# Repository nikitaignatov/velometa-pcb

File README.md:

# velometa pcb

Here be pcb stuff

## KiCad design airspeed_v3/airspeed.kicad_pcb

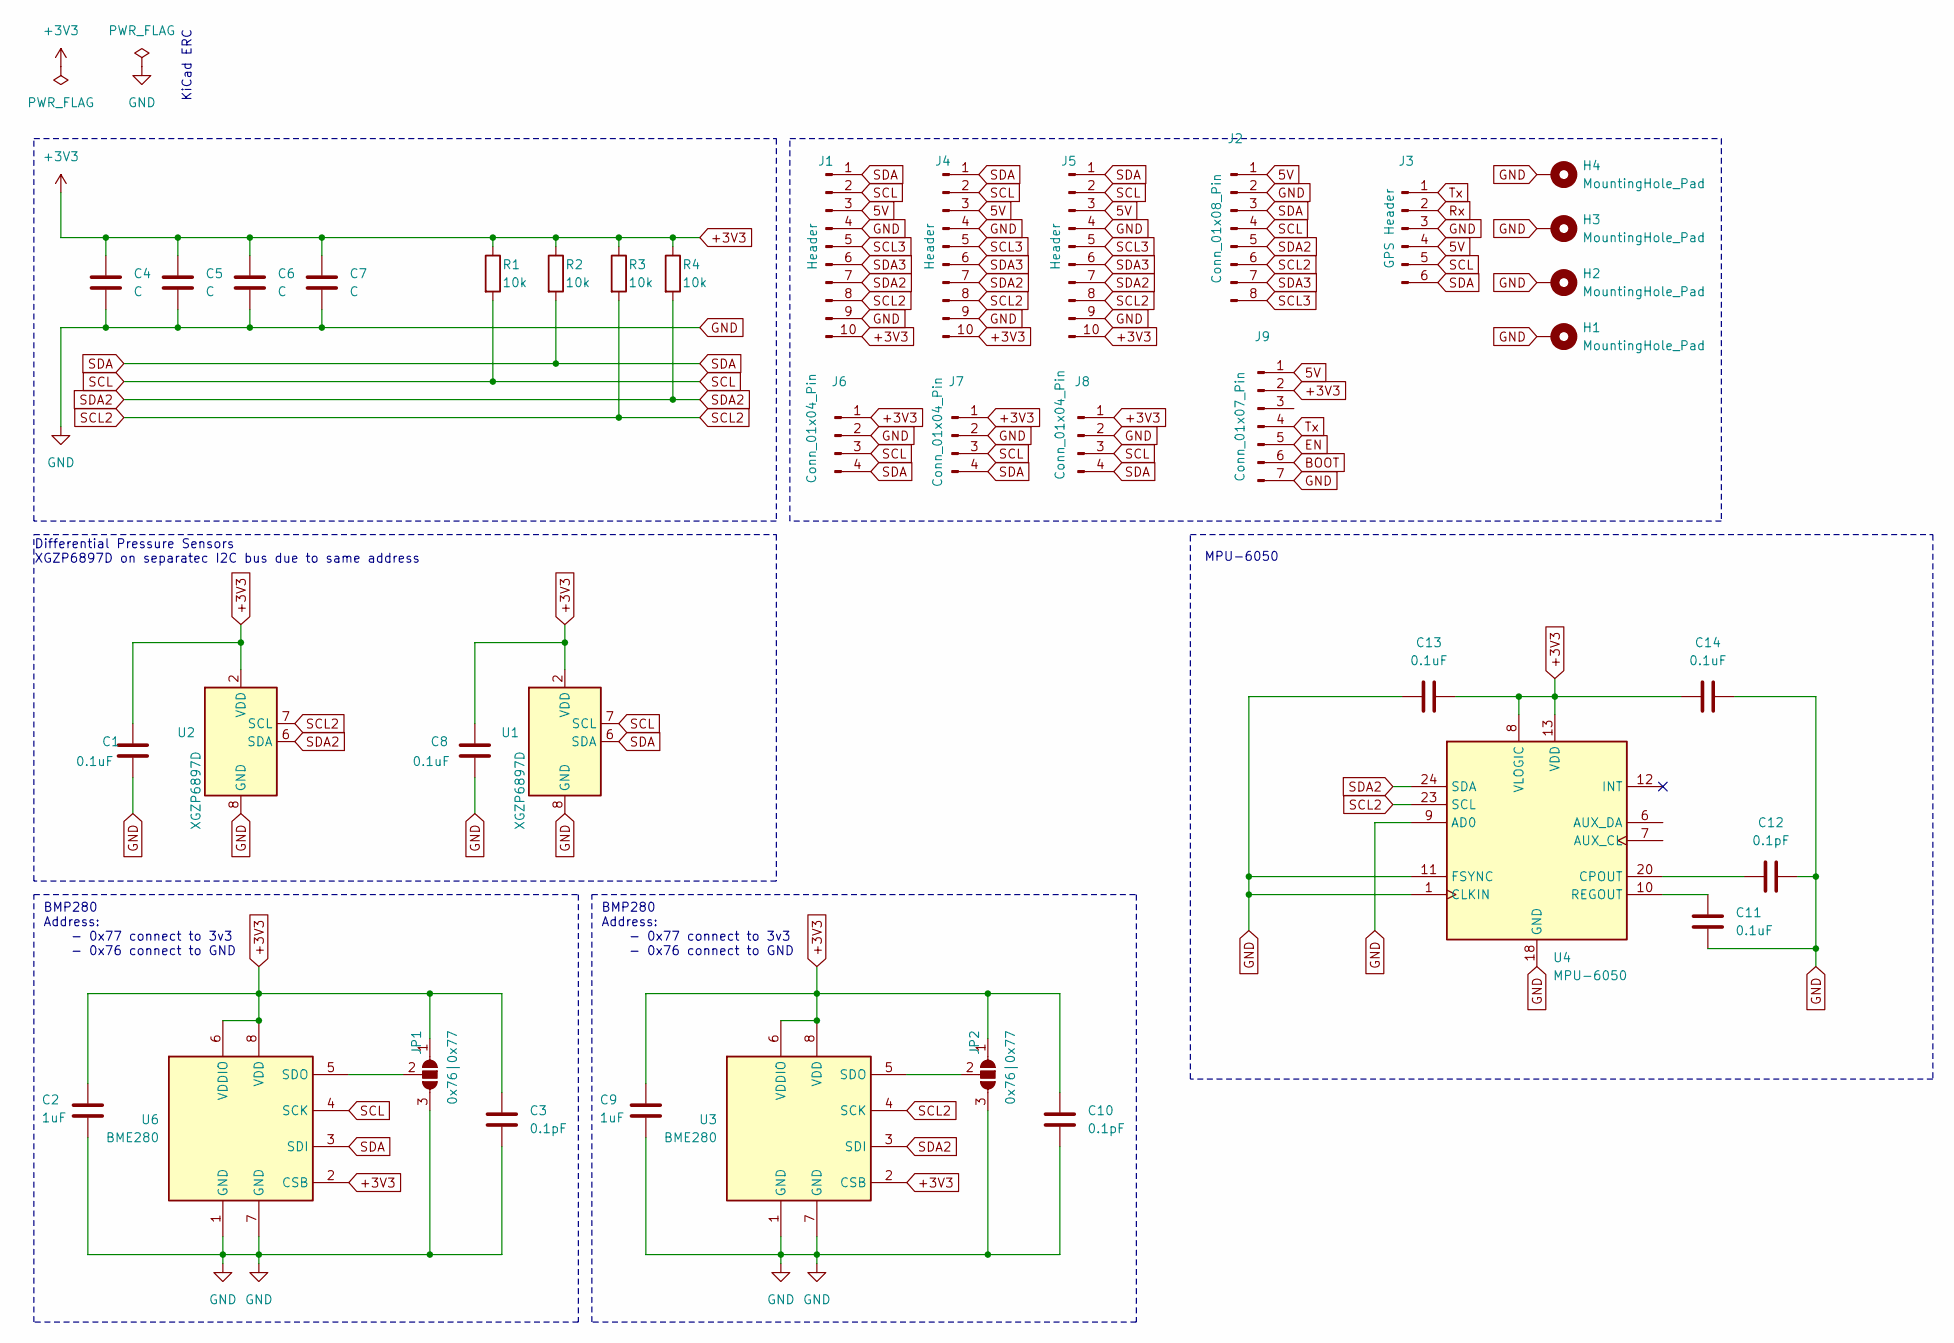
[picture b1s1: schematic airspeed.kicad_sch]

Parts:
C1, C8: 0.1uF
C2, C9: 1uF; C_0805_2012Metric
C3, C10, C12: 0.1pF; C_0805_2012Metric
C4, C5, C6: C; C_0805_2012Metric
C7: C
C11, C13, C14: 0.1uF; C_0805_2012Metric
H1, H2, H3, H4: MountingHole_Pad; MountingHole_2.7mm_M2.5_ISO14580_Pad
J1, J5: Header; PinHeader_1x10_P1.27mm_Vertical
J2: Conn_01x08_Pin; Molex_PicoBlade_53047-0810_1x08_P1.25mm_Vertical
J3: GPS Header; PinHeader_1x06_P1.27mm_Vertical
J4: Header; PinHeader_1x10_P2.00mm_Vertical
J6, J7, J8: Conn_01x04_Pin; PinHeader_1x04_P1.27mm_Vertical
J9: Conn_01x07_Pin; Molex_PicoBlade_53047-0710_1x07_P1.25mm_Vertical
JP1, JP2: 0x76|0x77; SolderJumper-3_P1.3mm_Open_RoundedPad1.0x1.5mm
R1, R2, R3, R4: 10k; R_0805_2012Metric
U1, U2: XGZP6897D; CFSensor_XGZP6897x
U3, U6: BME280; Bosch_LGA-8_2.5x2.5mm_P0.65mm_ClockwisePinNumbering
U4: MPU-6050; InvenSense_QFN-24_4x4mm_P0.5mm

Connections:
5V: J1.3, J2.1, J3.4, J4.3, J5.3, J9.1
+3V3: C1.1, C2.1, C3.1, C4.1, C5.1, C6.1, C7.1, C8.1, C9.1, C10.1, C13.2, C14.1, J1.10, J4.10, J5.10, J6.1, J7.1, J8.1, J9.2, JP1.1 (A), JP2.1 (A), R1.1, R2.1, R3.1, R4.1, U1.2 (VDD), U2.2 (VDD), U3.2 (CSB), U3.6 (VDDIO), U3.8 (VDD), U4.8 (VLOGIC), U4.13 (VDD), U6.2 (CSB), U6.6 (VDDIO), U6.8 (VDD)
BOOT: J9.6
EN: J9.5
GND: C1.2, C2.2, C3.2, C4.2, C5.2, C6.2, C7.2, C8.2, C9.2, C10.2, C11.2, C12.2, C13.1, C14.2, H1.1, H2.1, H3.1, H4.1, J1.4, J1.9, J2.2, J3.3, J4.4, J4.9, J5.4, J5.9, J6.2, J7.2, J8.2, J9.7, JP1.3 (B), JP2.3 (B), U1.8 (GND), U2.8 (GND), U3.1 (GND), U3.7 (GND), U4.1 (CLKIN), U4.9 (AD0), U4.11 (FSYNC), U4.18 (GND), U6.1 (GND), U6.7 (GND)
unnamed: JP1.2 (C), U6.5 (SDO)
unnamed: JP2.2 (C), U3.5 (SDO)
unnamed: C12.1, U4.20 (CPOUT)
unnamed: C11.1, U4.10 (REGOUT)
Rx: J3.2
SCL: J1.2, J2.4, J3.5, J4.2, J5.2, J6.3, J7.3, J8.3, R1.2, U1.7 (SCL), U6.4 (SCK)
SCL2: J1.8, J2.6, J4.8, J5.8, R3.2, U2.7 (SCL), U3.4 (SCK), U4.23 (SCL)
SCL3: J1.5, J2.8, J4.5, J5.5
SDA: J1.1, J2.3, J3.6, J4.1, J5.1, J6.4, J7.4, J8.4, R2.2, U1.6 (SDA), U6.3 (SDI)
SDA2: J1.7, J2.5, J4.7, J5.7, R4.2, U2.6 (SDA), U3.3 (SDI), U4.24 (SDA)
SDA3: J1.6, J2.7, J4.6, J5.6
Tx: J3.1, J9.4

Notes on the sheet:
BMP280 Address: - 0x77 connect to 3v3 - 0x76 connect to GND
KiCad ERC
Differential Pressure Sensors XGZP6897D on separatec I2C bus due to same address
MPU-6050

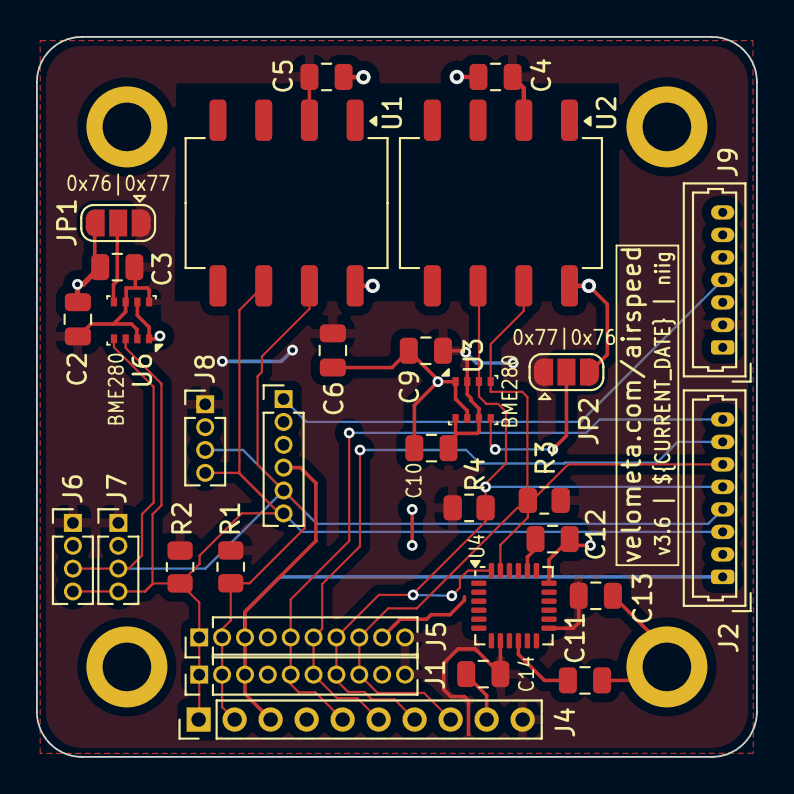
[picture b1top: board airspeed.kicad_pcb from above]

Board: 2 copper layers, 40.0 x 40.0 mm, 35 parts (0 on the bottom side), 14 nets.

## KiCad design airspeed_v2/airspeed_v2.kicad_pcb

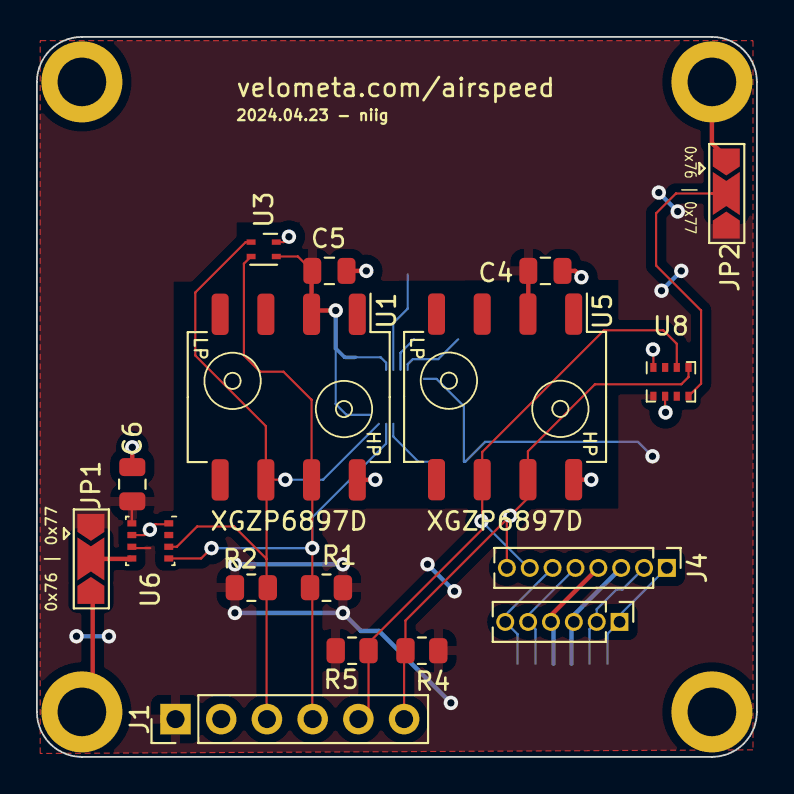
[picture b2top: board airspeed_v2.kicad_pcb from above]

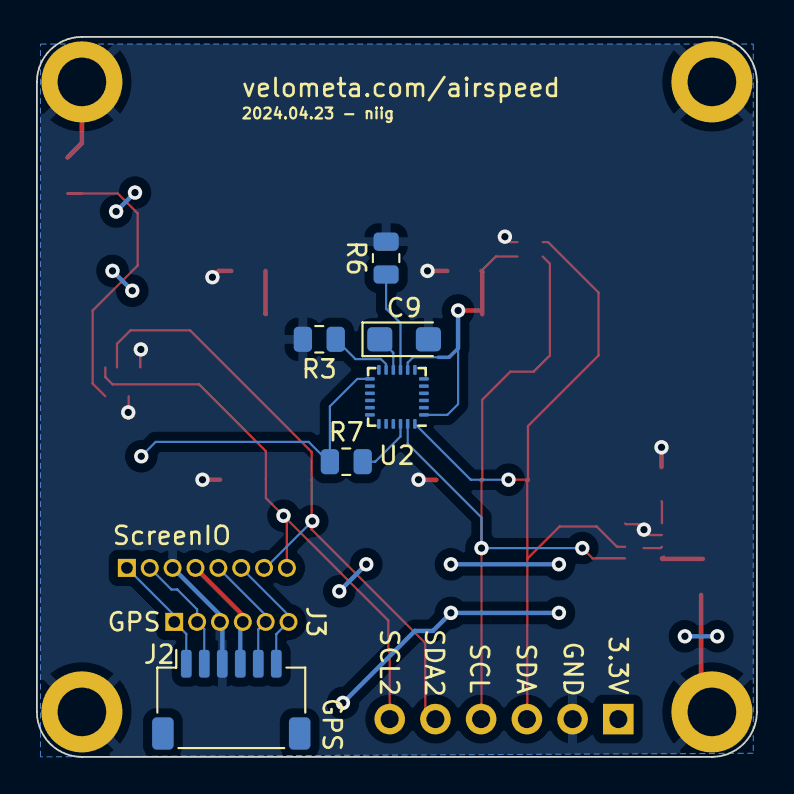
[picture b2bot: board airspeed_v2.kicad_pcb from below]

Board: 2 copper layers, 40.0 x 40.0 mm, 27 parts (6 on the bottom side), 15 nets.

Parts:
C4, C5, C6: C; C_0805_2012Metric
C9: 0.1pF; CP_EIA-3216-18_Kemet-A
H1, H2, H3, H4: MountingHole_Pad; MountingHole_2.7mm_M2.5_ISO14580_Pad
J1: Header; PinHeader_1x06_P2.54mm_Vertical
J2: GPS; JST_SH_SM06B-SRSS-TB_1x06-1MP_P1.00mm_Horizontal
J3: GPS; PinHeader_1x06_P1.27mm_Vertical
J4: ScreenIO; PinHeader_1x08_P1.27mm_Vertical
JP1, JP2: 0x76 | 0x77; SolderJumper-3_P2.0mm_Open_TrianglePad1.0x1.5mm
R1, R2, R3, R4, R5, R6, R7: 10k; R_0805_2012Metric
U1, U5: XGZP6897D; CFSensor_XGZP6897x
U2: MPU-9250; InvenSense_QFN-24_3x3mm_P0.4mm
U3: SHT4x; Sensirion_DFN-4_1.5x1.5mm_P0.8mm_SHT4x_NoCentralPad
U6: BME280; Bosch_LGA-8_2.5x2.5mm_P0.65mm_ClockwisePinNumbering
U8: BMP280; Bosch_LGA-8_2x2.5mm_P0.65mm_ClockwisePinNumbering

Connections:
5V: J2.4, J3.4, J4.4
+3V3: C4.1, C5.1, C6.1, J1.1, JP1.1 (A), JP2.3 (B), R1.1, R2.1, R4.1, R5.1, R7.1, U1.2 (VDD), U2.1 (RESV_VDDIO), U2.8 (VDDIO), U2.13 (VDD), U3.3 (VDD), U5.2 (VDD), U6.2 (CSB), U6.6 (VDDIO), U6.8 (VDD), U8.6 (VDDIO), U8.8 (VDD)
GND: C4.2, C5.2, C6.2, C9.2, H1.1, H2.1, H3.1, H4.1, J1.2, J2.3, J3.3, J4.3, JP1.3 (B), JP2.1 (A), R3.2, R6.2, U1.8 (GND), U2.18 (GND), U2.20 (RESV_GND), U3.4 (VSS), U5.8 (GND), U6.1 (GND), U6.7 (GND), U8.1 (GND), U8.7 (GND)
unnamed: JP1.2 (C), U6.5 (SDO)
unnamed: JP2.2 (C), U8.5 (SDO)
unnamed: R6.1, U2.9 (AD0/MISO)
unnamed: R3.1, U2.11 (FSYNC)
unnamed: C9.1, U2.10 (REGOUT)
unnamed: R7.2, U2.22 (~CS)
Rx: J2.1, J3.1, J4.1
SCL: J1.4, J2.5, J3.5, J4.5, R1.2, U1.7 (SCL), U2.23 (SCL/SCLK), U3.2 (SCL), U6.4 (SCK)
SCL2: J1.6, J4.8, R4.2, U5.7 (SCL), U8.4 (SCK)
SDA: J1.3, J2.6, J3.6, J4.6, R2.2, U1.6 (SDA), U2.24 (SDA/MOSI), U3.1 (SDA), U6.3 (SDI)
SDA2: J1.5, J4.7, R5.2, U5.6 (SDA), U8.3 (SDI)
Tx: J2.2, J3.2, J4.2

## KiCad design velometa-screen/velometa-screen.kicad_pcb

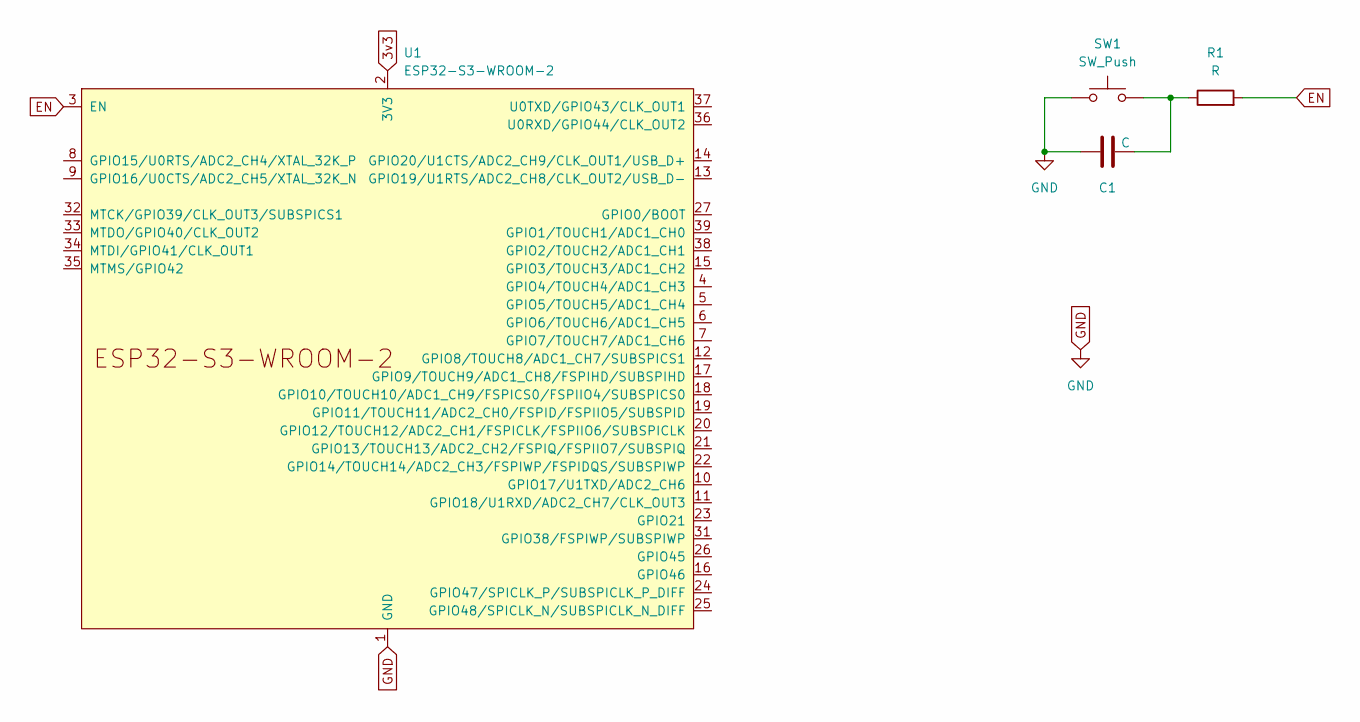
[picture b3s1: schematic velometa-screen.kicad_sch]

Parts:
C1: C; C_0805_2012Metric
R1: R; R_0805_2012Metric
SW1: SW_Push; SW_SPST_EVQP7A
U1: ESP32-S3-WROOM-2

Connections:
3v3: U1.2 (3V3)
EN: R1.2, U1.3 (EN)
GND: C1.1, SW1.1, U1.1 (GND), U1.40 (GND), U1.41 (GND)
unnamed: C1.2, R1.1, SW1.2

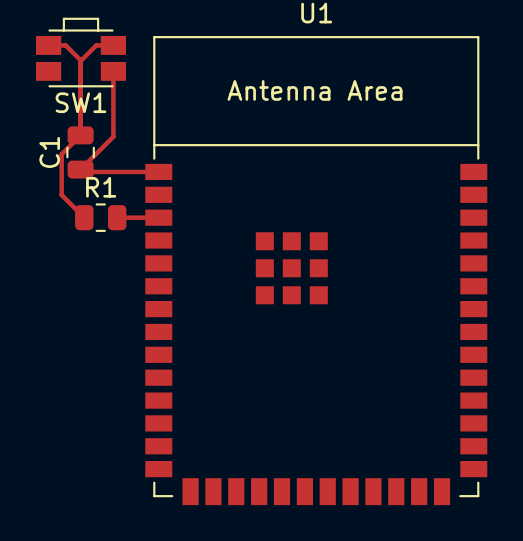
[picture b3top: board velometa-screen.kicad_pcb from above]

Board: 2 copper layers, 4 parts (0 on the bottom side), 3 nets.

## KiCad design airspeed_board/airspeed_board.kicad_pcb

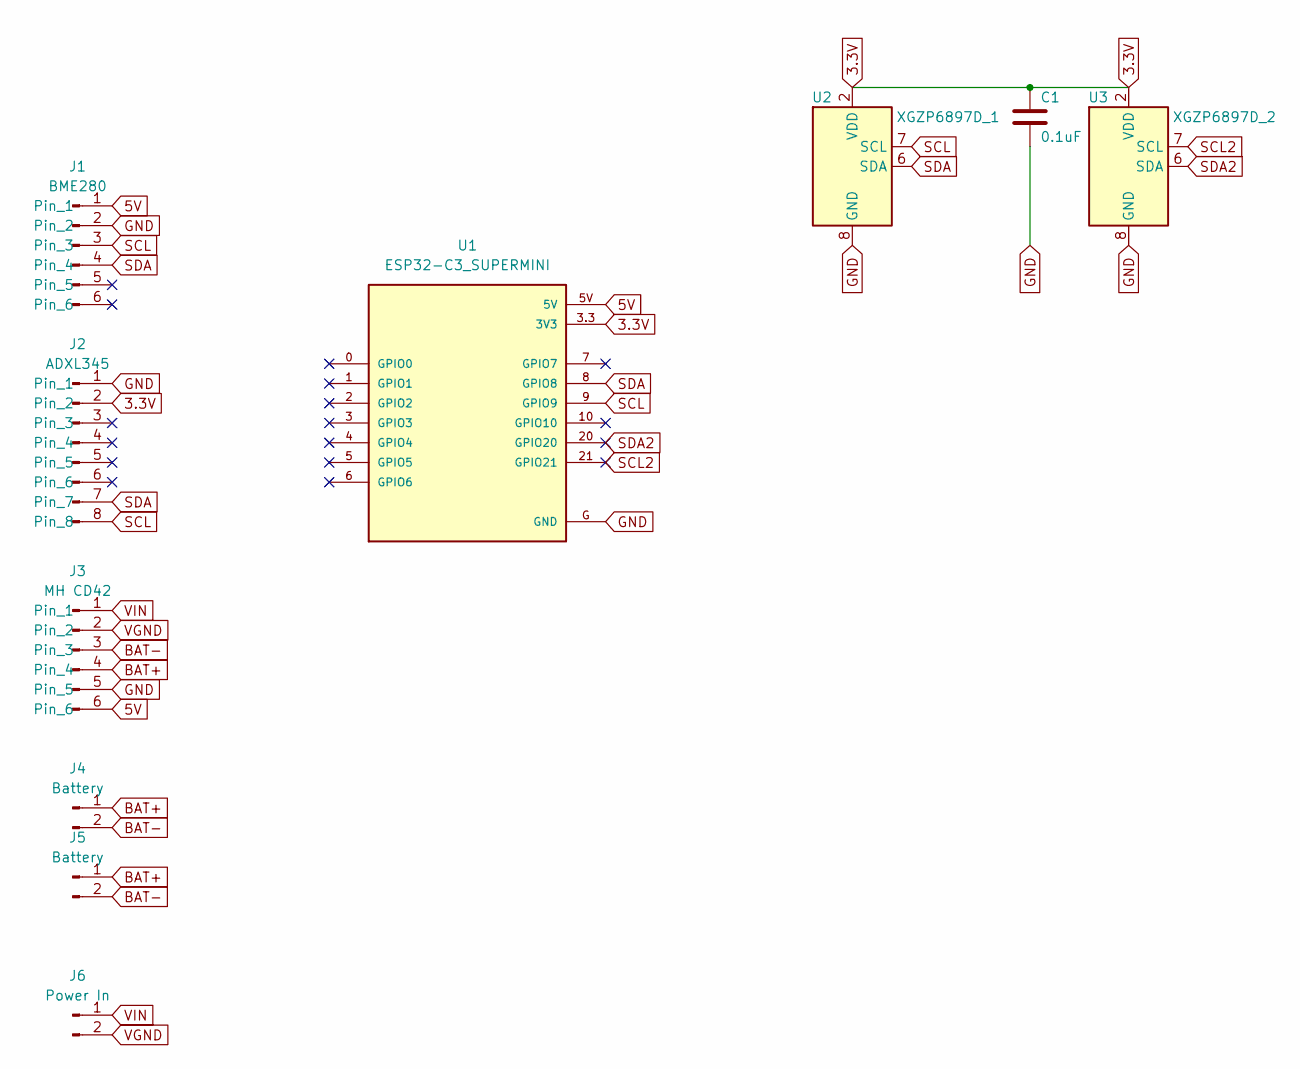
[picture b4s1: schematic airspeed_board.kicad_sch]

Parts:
C1: 0.1uF; C_0805_2012Metric
J1: BME280; PinHeader_1x06_P2.54mm_Vertical
J2: ADXL345; PinHeader_1x08_P2.54mm_Vertical
J3: MH CD42; PinHeader_1x06_P2.54mm_Vertical
J4: Battery; PinSocket_1x02_P2.54mm_Vertical
J5: Battery; PinSocket_1x02_P1.27mm_Vertical
J6: Power In; PinHeader_1x02_P2.54mm_Vertical
U1: ESP32-C3_SUPERMINI; MODULE_ESP32-C3_SUPERMINI
U2: XGZP6897D_1; CFSensor_XGZP6897x
U3: XGZP6897D_2; CFSensor_XGZP6897x

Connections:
3.3V: C1.2, J2.2, U1.3.3 (3V3), U2.2 (VDD), U3.2 (VDD)
5V: J1.1, J3.6, U1.5V
BAT+: J3.4, J4.1, J5.1
BAT-: J3.3, J4.2, J5.2
GND: C1.1, J1.2, J2.1, J3.5, U1.G (GND), U2.8 (GND), U3.8 (GND)
SCL: J1.3, J2.8, U1.9 (GPIO9), U2.7 (SCL)
SCL2: U1.21 (GPIO21), U3.7 (SCL)
SDA: J1.4, J2.7, U1.8 (GPIO8), U2.6 (SDA)
SDA2: U1.20 (GPIO20), U3.6 (SDA)
VGND: J3.2, J6.2
VIN: J3.1, J6.1

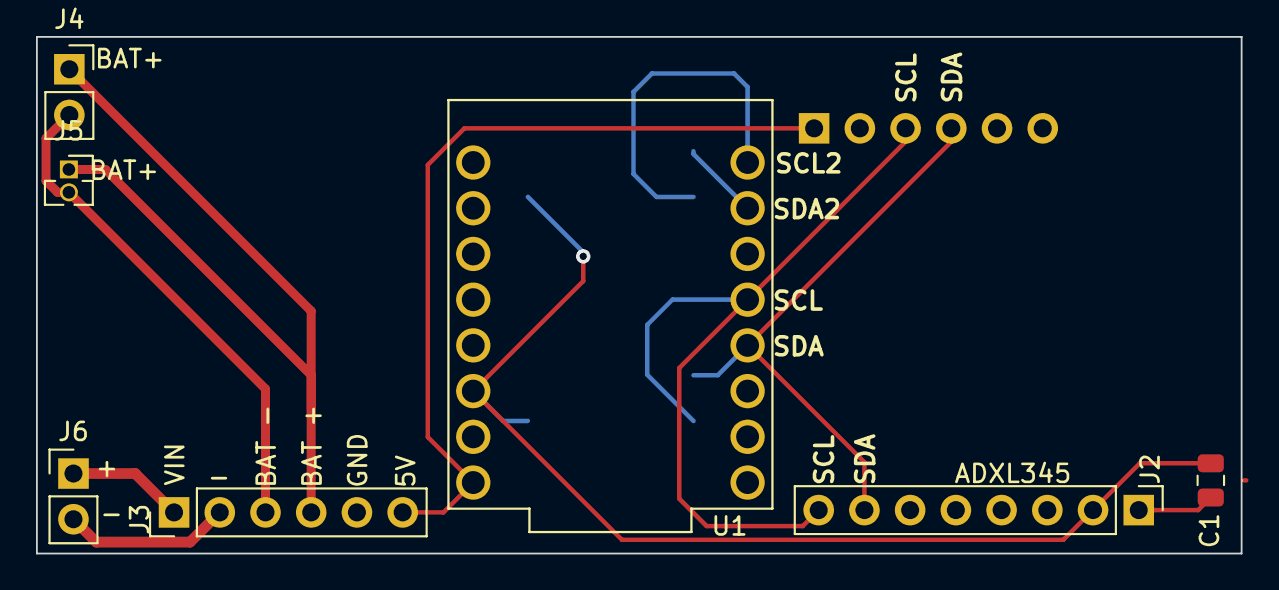
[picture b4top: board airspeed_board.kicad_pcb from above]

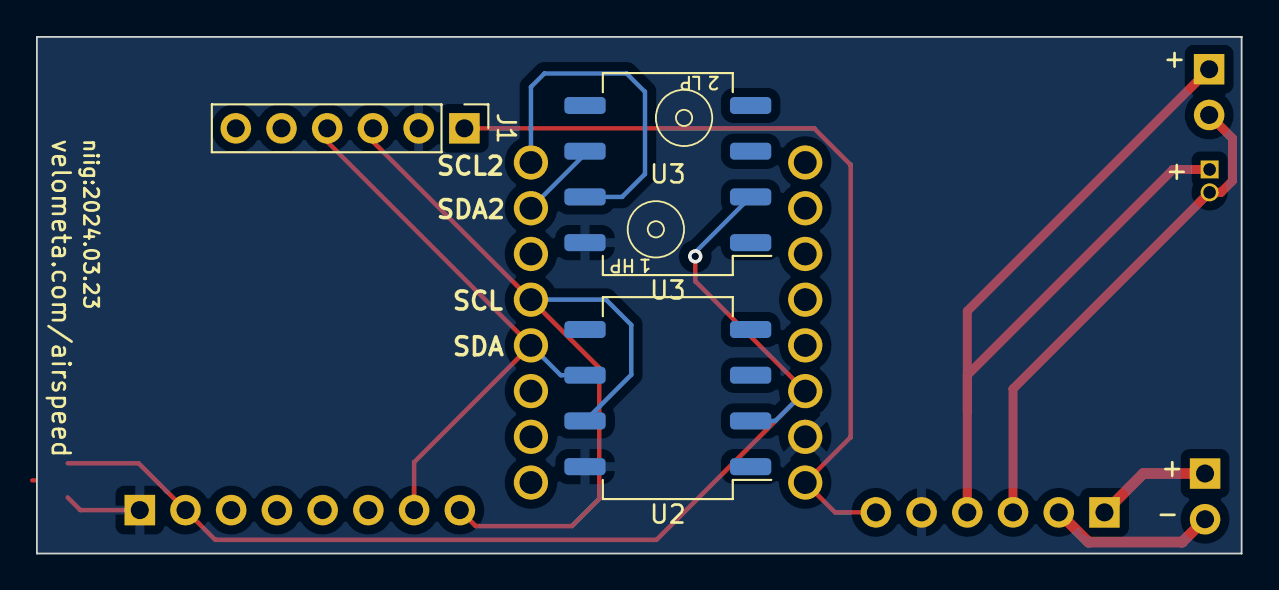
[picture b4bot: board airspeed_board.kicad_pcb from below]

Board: 2 copper layers, 66.9 x 28.7 mm, 10 parts (3 on the bottom side), 11 nets.

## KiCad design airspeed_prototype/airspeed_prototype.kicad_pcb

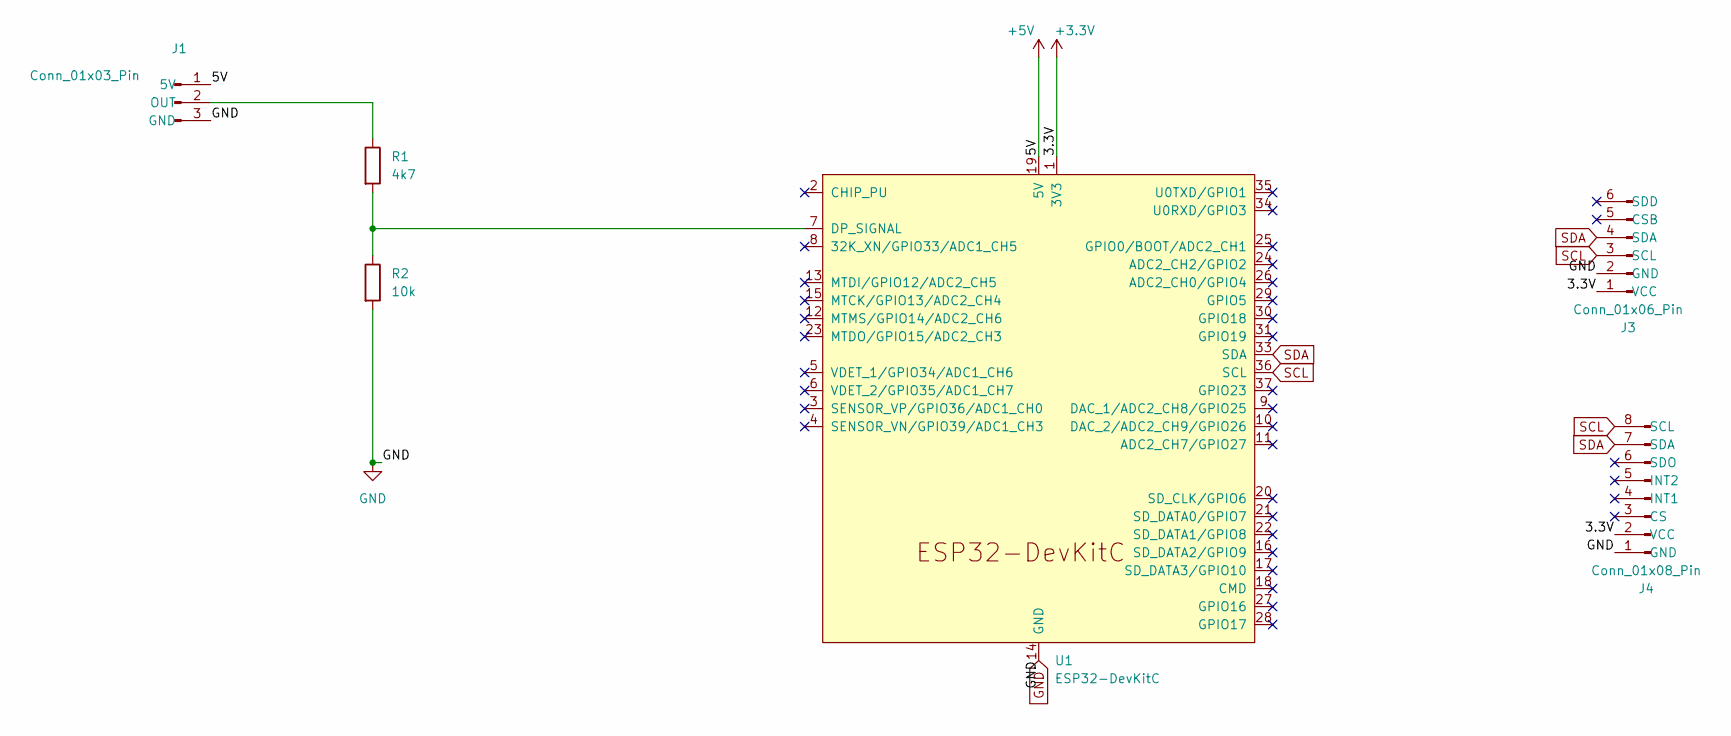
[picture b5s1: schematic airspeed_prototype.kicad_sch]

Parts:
J1: Conn_01x03_Pin; PinHeader_1x03_P2.54mm_Vertical
J3: Conn_01x06_Pin; PinHeader_1x06_P2.54mm_Vertical
J4: Conn_01x08_Pin; PinHeader_1x08_P2.54mm_Vertical
R1: 4k7; R_0805_2012Metric
R2: 10k; R_0805_2012Metric
U1: ESP32-DevKitC

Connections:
+3.3V: J3.1 (VCC), J4.2 (VCC), U1.1 (3V3)
+5V: J1.1 (5V), U1.19 (5V)
GND: J1.3 (GND), J3.2 (GND), J4.1 (GND), R2.2, U1.14 (GND), U1.32 (GND), U1.38 (GND)
unnamed: J1.2 (OUT), R1.1
unnamed: R1.2, R2.1, U1.7 (DP_SIGNAL)
SCL: J3.3 (SCL), J4.8 (SCL), U1.36 (SCL)
SDA: J3.4 (SDA), J4.7 (SDA), U1.33 (SDA)

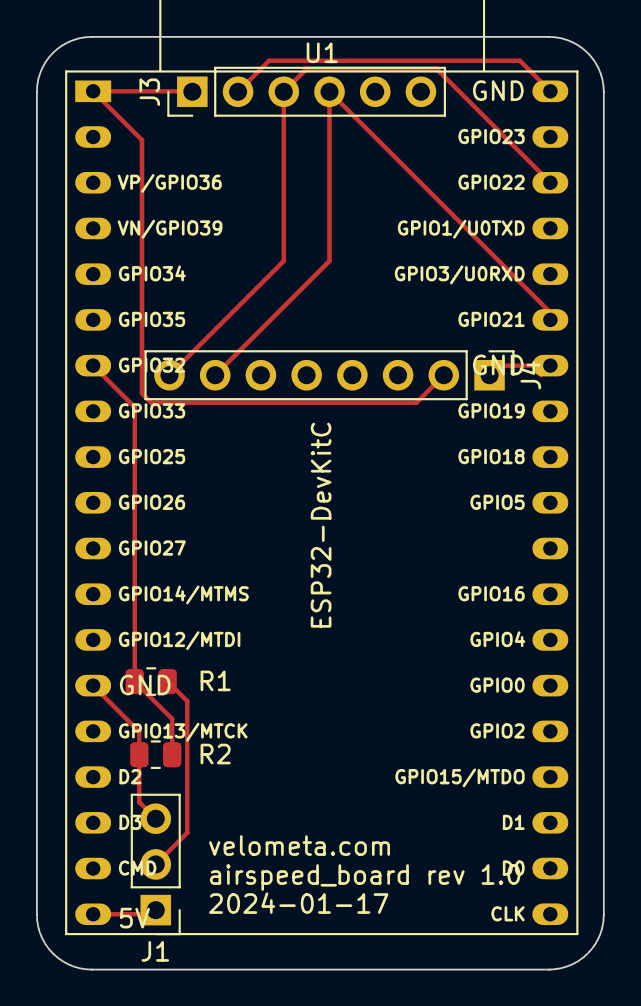
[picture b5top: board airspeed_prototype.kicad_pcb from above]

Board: 2 copper layers, 31.5 x 51.8 mm, 6 parts (0 on the bottom side), 7 nets.

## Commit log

2024-01-13 created project
2024-01-13 some experiment
2024-01-13 test
2024-01-15 schematic
2024-01-16 update the schematic and pcb
2024-02-01 updates to pcb
2024-02-08 ignore file
2024-02-08 new pcb layout
2024-02-18 new board with 2 pressure sensors
2024-02-19 updated board layout
2024-03-24 update fix the power for bme and battery connector
2024-03-24 screen board
2024-04-18 airspeed_v2 pcdb
2024-04-27 airspeed v3
2024-04-27 airspeed v2
2024-04-28 complete airspeed v3.2
2024-04-28 upgrade to kicad v8
2024-04-28 labels alignment
2024-04-28 update footprint with latest from kicad8
2024-04-28 fix label
2024-04-28 updated the schematic to use latest bp280
2024-04-28 added BOM file
2024-04-28 remove BOM file
2024-05-03 v3.4
2024-05-14 airspeed v3.6
